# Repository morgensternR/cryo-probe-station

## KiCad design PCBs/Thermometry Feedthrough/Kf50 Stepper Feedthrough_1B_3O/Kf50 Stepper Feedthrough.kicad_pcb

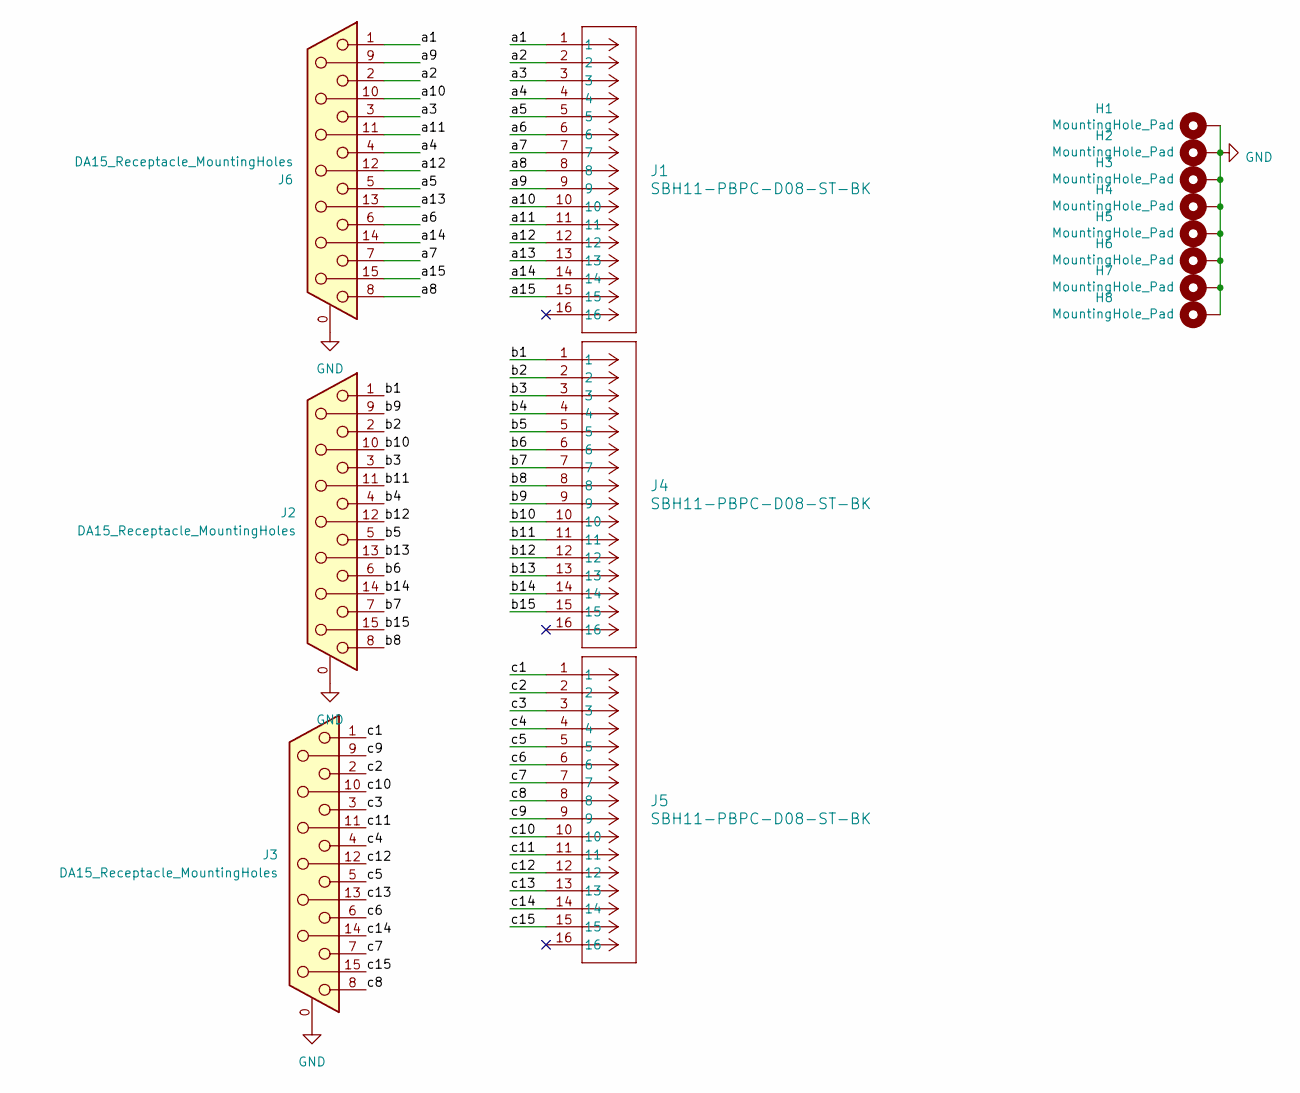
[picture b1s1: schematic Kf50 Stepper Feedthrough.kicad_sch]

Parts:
H1, H2, H3, H4, H5, H6, H7, H8: MountingHole_Pad; MountingHole_5mm_Pad
J1, J4, J5: SBH11-PBPC-D08-ST-BK; CONN16_SBH11-PBPC-D08-ST-BK_SUL
J2, J3, J6: DA15_Receptacle_MountingHoles; DSUB-15_Male_Vertical_P2.77x2.84mm_MountingHoles; LCSC C599294

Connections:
/a1: J1.1, J6.1
/a2: J1.2, J6.2
/a3: J1.3, J6.3
/a4: J1.4, J6.4
/a5: J1.5, J6.5
/a6: J1.6, J6.6
/a7: J1.7, J6.7
/a8: J1.8, J6.8
/a9: J1.9, J6.9
/a10: J1.10, J6.10
/a11: J1.11, J6.11 (P111)
/a12: J1.12, J6.12
/a13: J1.13, J6.13
/a14: J1.14, J6.14
/a15: J1.15, J6.15
/b1: J2.1, J4.1
/b2: J2.2, J4.2
/b3: J2.3, J4.3
/b4: J2.4, J4.4
/b5: J2.5, J4.5
/b6: J2.6, J4.6
/b7: J2.7, J4.7
/b8: J2.8, J4.8
/b9: J2.9, J4.9
/b10: J2.10, J4.10
/b11: J2.11 (P111), J4.11
/b12: J2.12, J4.12
/b13: J2.13, J4.13
/b14: J2.14, J4.14
/b15: J2.15, J4.15
/c1: J3.1, J5.1
/c2: J3.2, J5.2
/c3: J3.3, J5.3
/c4: J3.4, J5.4
/c5: J3.5, J5.5
/c6: J3.6, J5.6
/c7: J3.7, J5.7
/c8: J3.8, J5.8
/c9: J3.9, J5.9
/c10: J3.10, J5.10
/c11: J3.11 (P111), J5.11
/c12: J3.12, J5.12
/c13: J3.13, J5.13
/c14: J3.14, J5.14
/c15: J3.15, J5.15
GND: H1.1, H2.1, H3.1, H4.1, H5.1, H6.1, H7.1, H8.1, J2.0 (PAD), J3.0 (PAD), J6.0 (PAD)

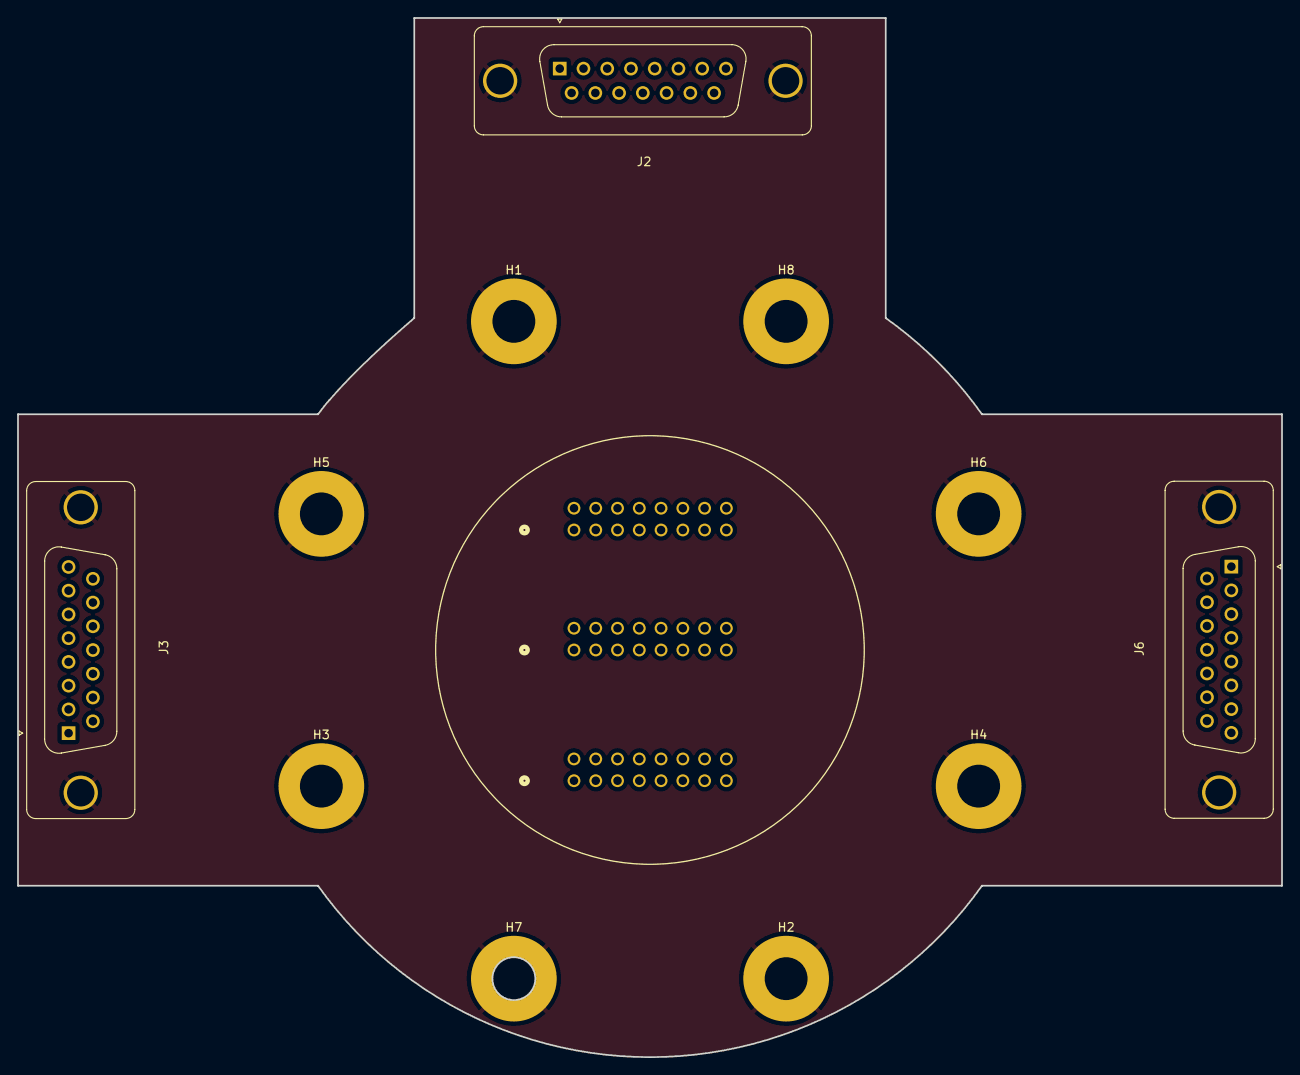
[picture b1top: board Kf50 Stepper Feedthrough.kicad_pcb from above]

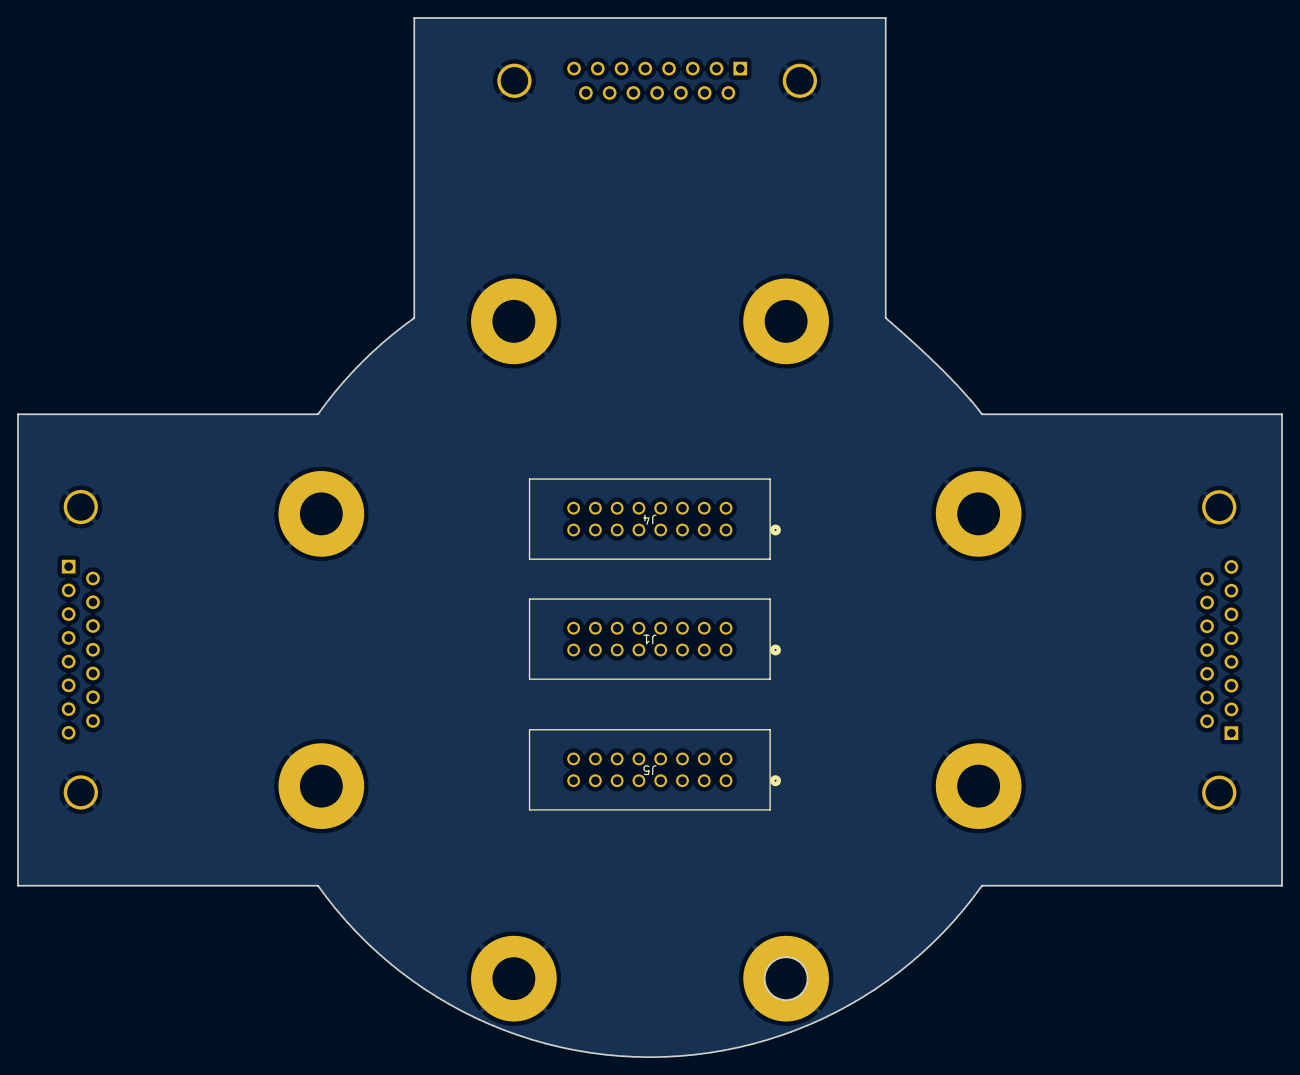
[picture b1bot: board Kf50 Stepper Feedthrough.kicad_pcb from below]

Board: 4 copper layers, 147.5 x 121.2 mm, 14 parts (3 on the bottom side), 46 nets.

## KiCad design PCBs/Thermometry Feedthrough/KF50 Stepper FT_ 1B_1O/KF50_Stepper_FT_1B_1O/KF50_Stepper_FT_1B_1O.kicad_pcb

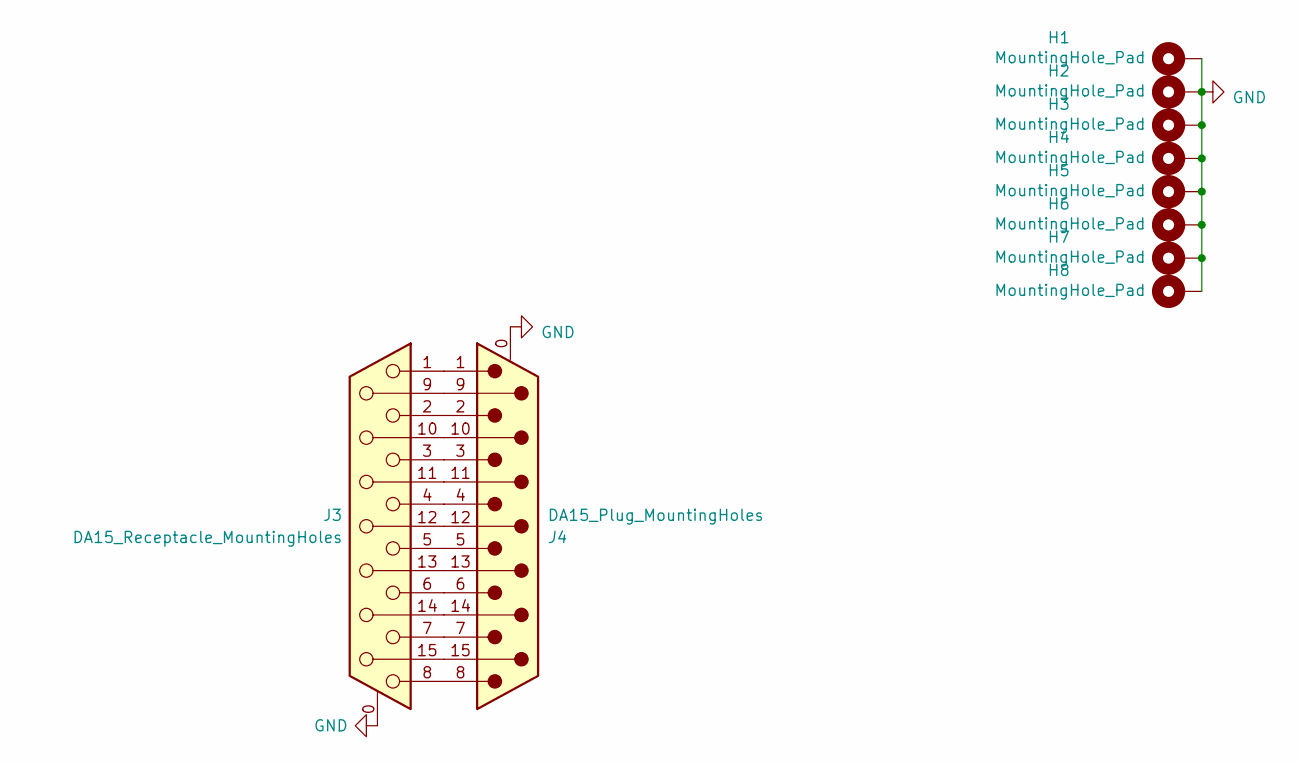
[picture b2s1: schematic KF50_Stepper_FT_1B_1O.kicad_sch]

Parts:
H1, H2, H3, H4, H5, H6, H7, H8: MountingHole_Pad; MountingHole_5mm_Pad
J3: DA15_Receptacle_MountingHoles; DB15-TH_TE_2301840-1; LCSC C591544
J4: DA15_Plug_MountingHoles; DSUB-TH_DS1037-15FN; LCSC C77837

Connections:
GND: H1.1, H2.1, H3.1, H4.1, H5.1, H6.1, H7.1, H8.1, J3.0 (PAD), J4.0 (PAD); also elsewhere on the board
unnamed: J3.9, J4.9
unnamed: J3.10, J4.10
unnamed: J3.12, J4.12
unnamed: J3.13, J4.13
unnamed: J3.14, J4.14
unnamed: J3.15, J4.15
unnamed: J3.11 (P111), J4.11 (P111)
unnamed: J3.1, J4.1
unnamed: J3.2, J4.2
unnamed: J3.3, J4.3
unnamed: J3.4, J4.4
unnamed: J3.5, J4.5
unnamed: J3.6, J4.6
unnamed: J3.7, J4.7
unnamed: J3.8, J4.8

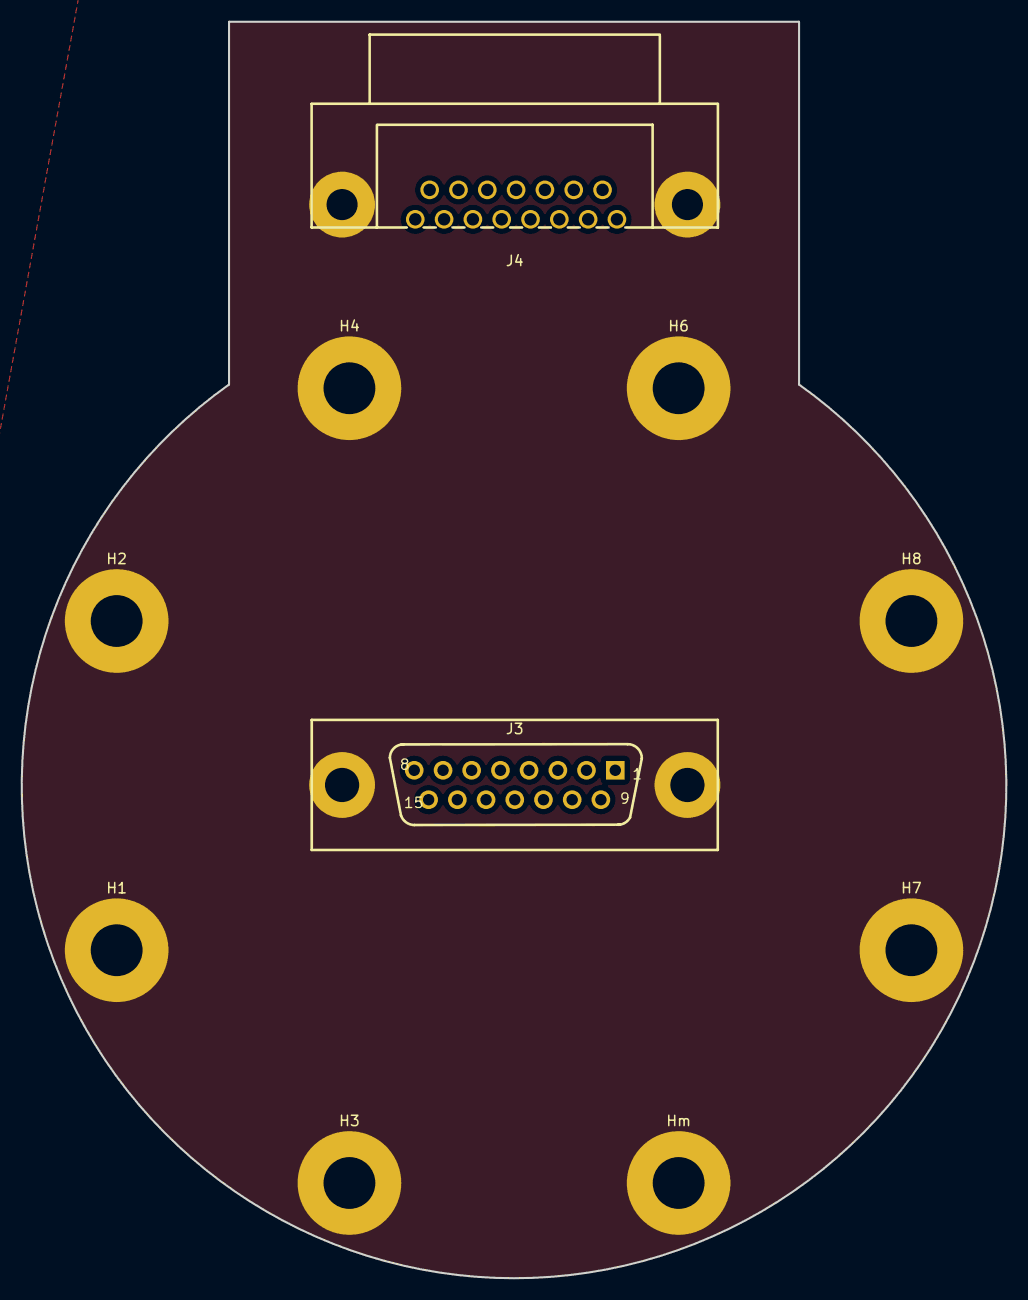
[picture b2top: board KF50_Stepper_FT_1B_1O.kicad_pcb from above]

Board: 4 copper layers, 95.0 x 121.2 mm, 10 parts (0 on the bottom side), 16 nets.

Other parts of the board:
Hm: MountingHole_Pad; MountingHole_5mm_Pad

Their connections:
GND: Hm.1; also elsewhere on the board

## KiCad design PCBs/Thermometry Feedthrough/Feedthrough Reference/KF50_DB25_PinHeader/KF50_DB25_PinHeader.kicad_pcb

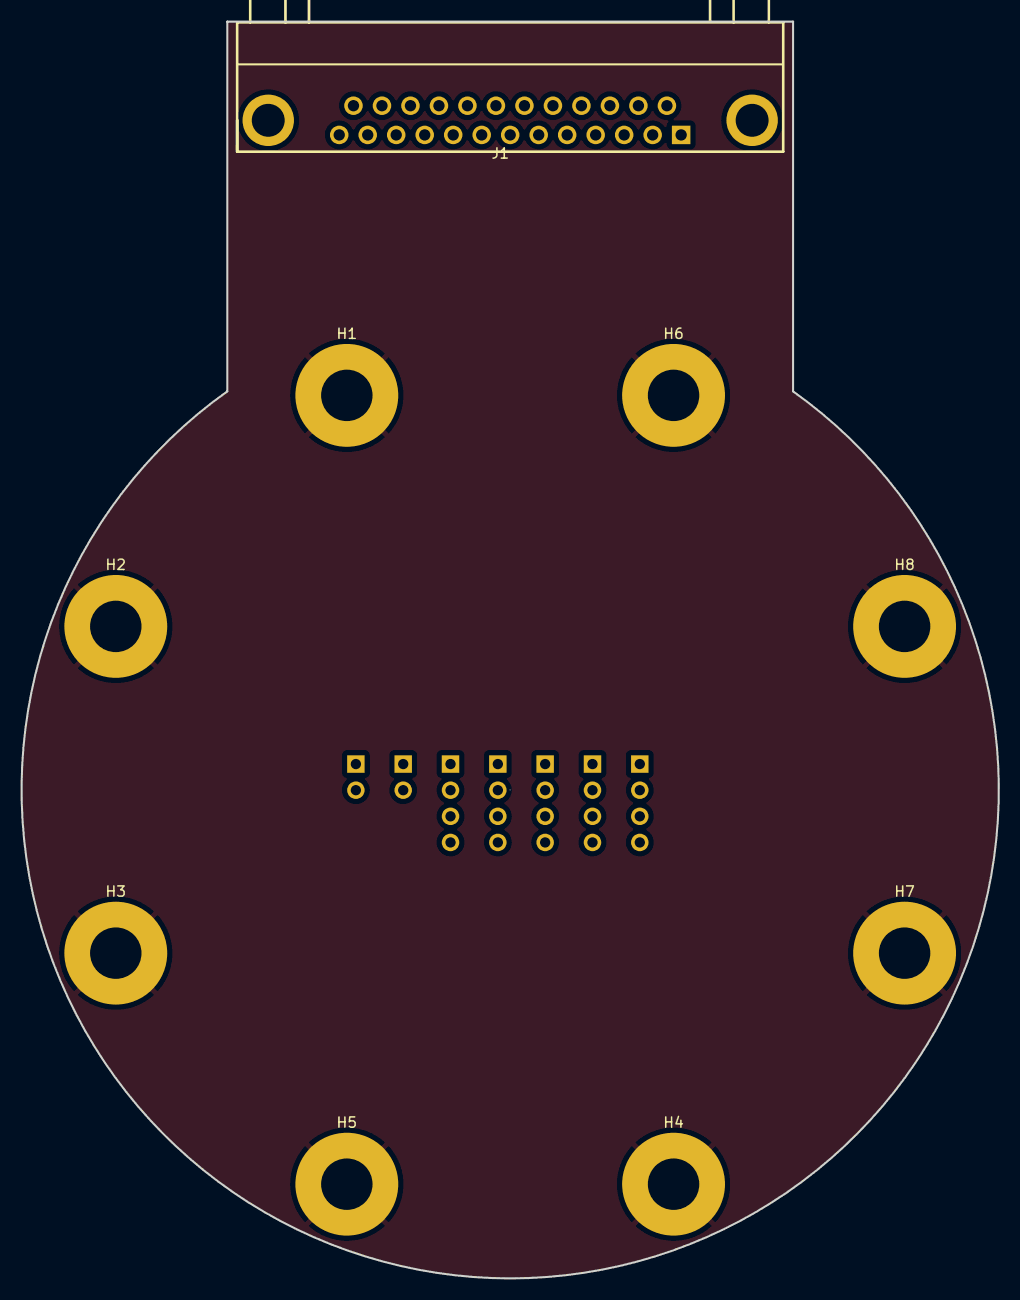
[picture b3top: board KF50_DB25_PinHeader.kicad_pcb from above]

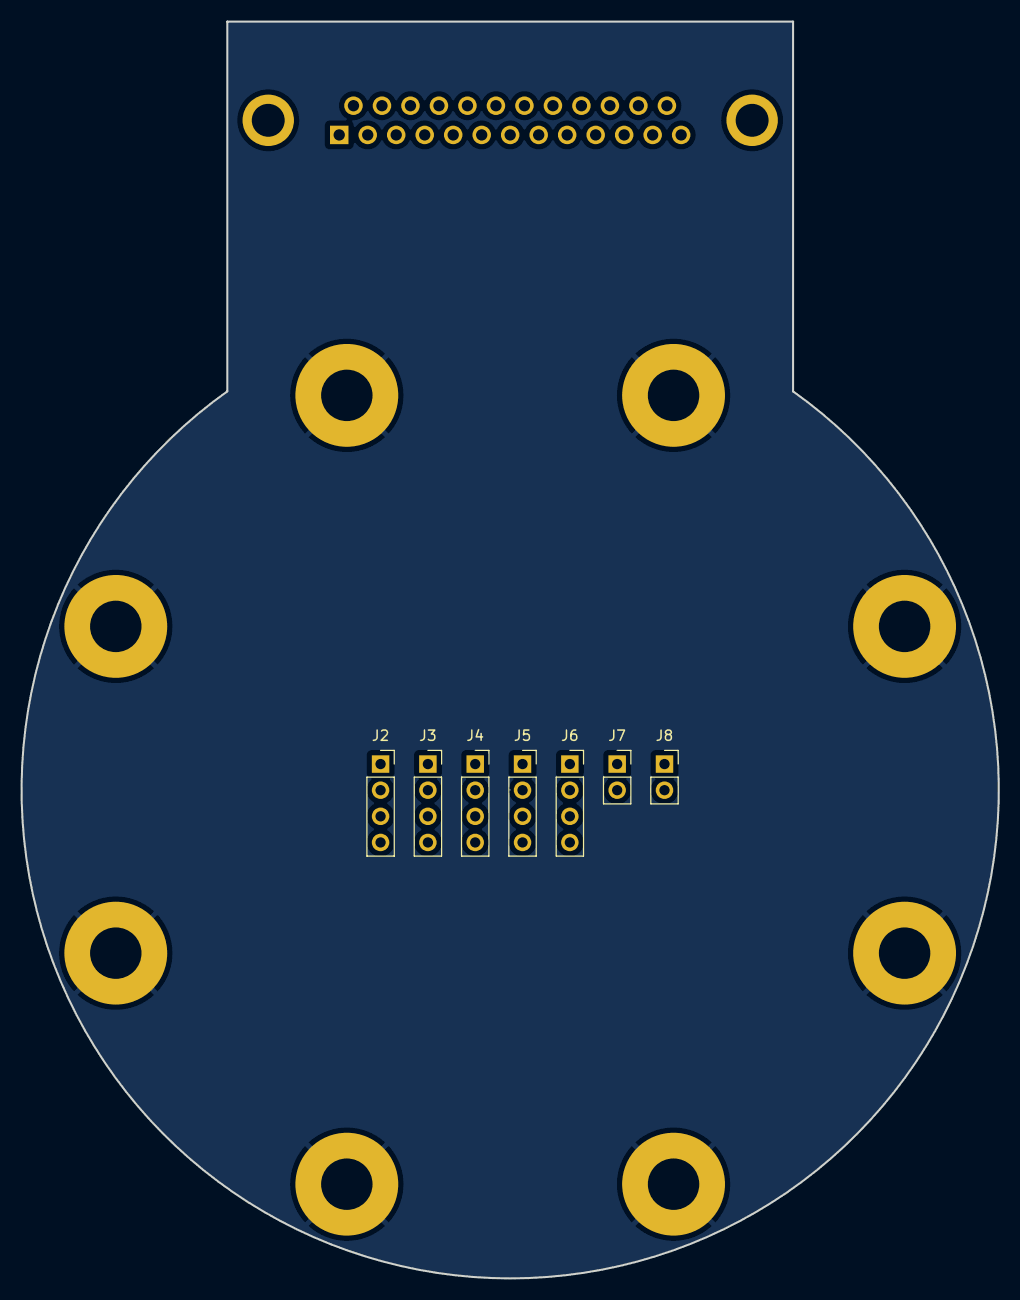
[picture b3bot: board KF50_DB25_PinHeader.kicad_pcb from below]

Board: 4 copper layers, 95.0 x 122.2 mm, 16 parts (7 on the bottom side), 25 nets.

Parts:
H1, H2, H3, H4, H5, H6, H7, H8: MountingHole_Pad; MountingHole_5mm_Pad
J1: DB25_Plug; DB25-TH_FDB2501-M0DB300K6KA
J2, J3, J4, J5, J6: Conn_01x04_Socket; PinSocket_1x04_P2.54mm_Vertical
J7, J8: Conn_01x02_Socket; PinSocket_1x02_P2.54mm_Vertical

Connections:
GND: H1.1, H2.1, H3.1, H4.1, H5.1, H6.1, H7.1, H8.1
unnamed: J1.14, J2.2
unnamed: J1.15, J2.4
unnamed: J1.16, J3.2
unnamed: J1.17, J3.4
unnamed: J1.18, J4.2
unnamed: J1.19, J4.4
unnamed: J1.20, J5.2
unnamed: J1.21, J5.4
unnamed: J1.22, J6.2
unnamed: J1.23, J6.4
unnamed: J1.24, J7.2
unnamed: J1.25, J8.2
unnamed: J1.1, J2.1
unnamed: J1.2, J2.3
unnamed: J1.3, J3.1
unnamed: J1.4, J3.3
unnamed: J1.5, J4.1
unnamed: J1.6, J4.3
unnamed: J1.7, J5.1
unnamed: J1.8, J5.3
unnamed: J1.9, J6.1
unnamed: J1.10, J6.3
unnamed: J1.11, J7.1
unnamed: J1.12, J8.1

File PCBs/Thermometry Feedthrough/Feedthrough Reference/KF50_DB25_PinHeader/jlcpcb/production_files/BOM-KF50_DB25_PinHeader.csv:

Comment,Designator,Footprint,LCSC
Conn_01x04_Socket,"J2,J3,J4,J5,J6",PinSocket_1x04_P2.54mm_Vertical,C2718488
DB25_Plug,J1,DB25-TH_FDB2501-M0DB300K6KA,C2834344
Conn_01x02_Socket,"J7,J8",PinSocket_1x02_P2.54mm_Vertical,C2935896
MountingHole_Pad,H8,MountingHole_5mm_Pad,
MountingHole_Pad,H7,MountingHole_5mm_Pad,
MountingHole_Pad,H6,MountingHole_5mm_Pad,
MountingHole_Pad,H5,MountingHole_5mm_Pad,
MountingHole_Pad,H4,MountingHole_5mm_Pad,
MountingHole_Pad,H3,MountingHole_5mm_Pad,
MountingHole_Pad,H2,MountingHole_5mm_Pad,
MountingHole_Pad,H1,MountingHole_5mm_Pad,

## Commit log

2024-02-26 Iniitial
2024-02-26 Mostly-recovered after Google Drive errors
2024-02-26 Working
2024-02-27 Working State to be reviewed
2024-02-29 changed mirror bend wall
2024-05-18 updated cad
2024-06-10 WIP before 2nd parts order
2024-06-10 Deleting old wafer holder
2024-06-10 Moving main assembly to base directory
2024-06-10 Moving KICAD PCBs to their own folder
2024-06-10 Rename isolation folder
2024-06-10 Rename "Probe Cad" to "Probe"
2024-06-11 remove junk assembly
2024-06-11 renaming and moving
2024-10-03 Latest
